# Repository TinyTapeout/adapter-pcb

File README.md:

# Tiny Tapeout adapter PCBs

For interfacing between different versions of the [carrier board](https://github.com/TinyTapeout/breakout-pcb/) and the [demo board](https://github.com/TinyTapeout/tt-demo-pcb)

## TT04 carrier board to TT06 demo board

## TT06 carrier board to TT04 demo board

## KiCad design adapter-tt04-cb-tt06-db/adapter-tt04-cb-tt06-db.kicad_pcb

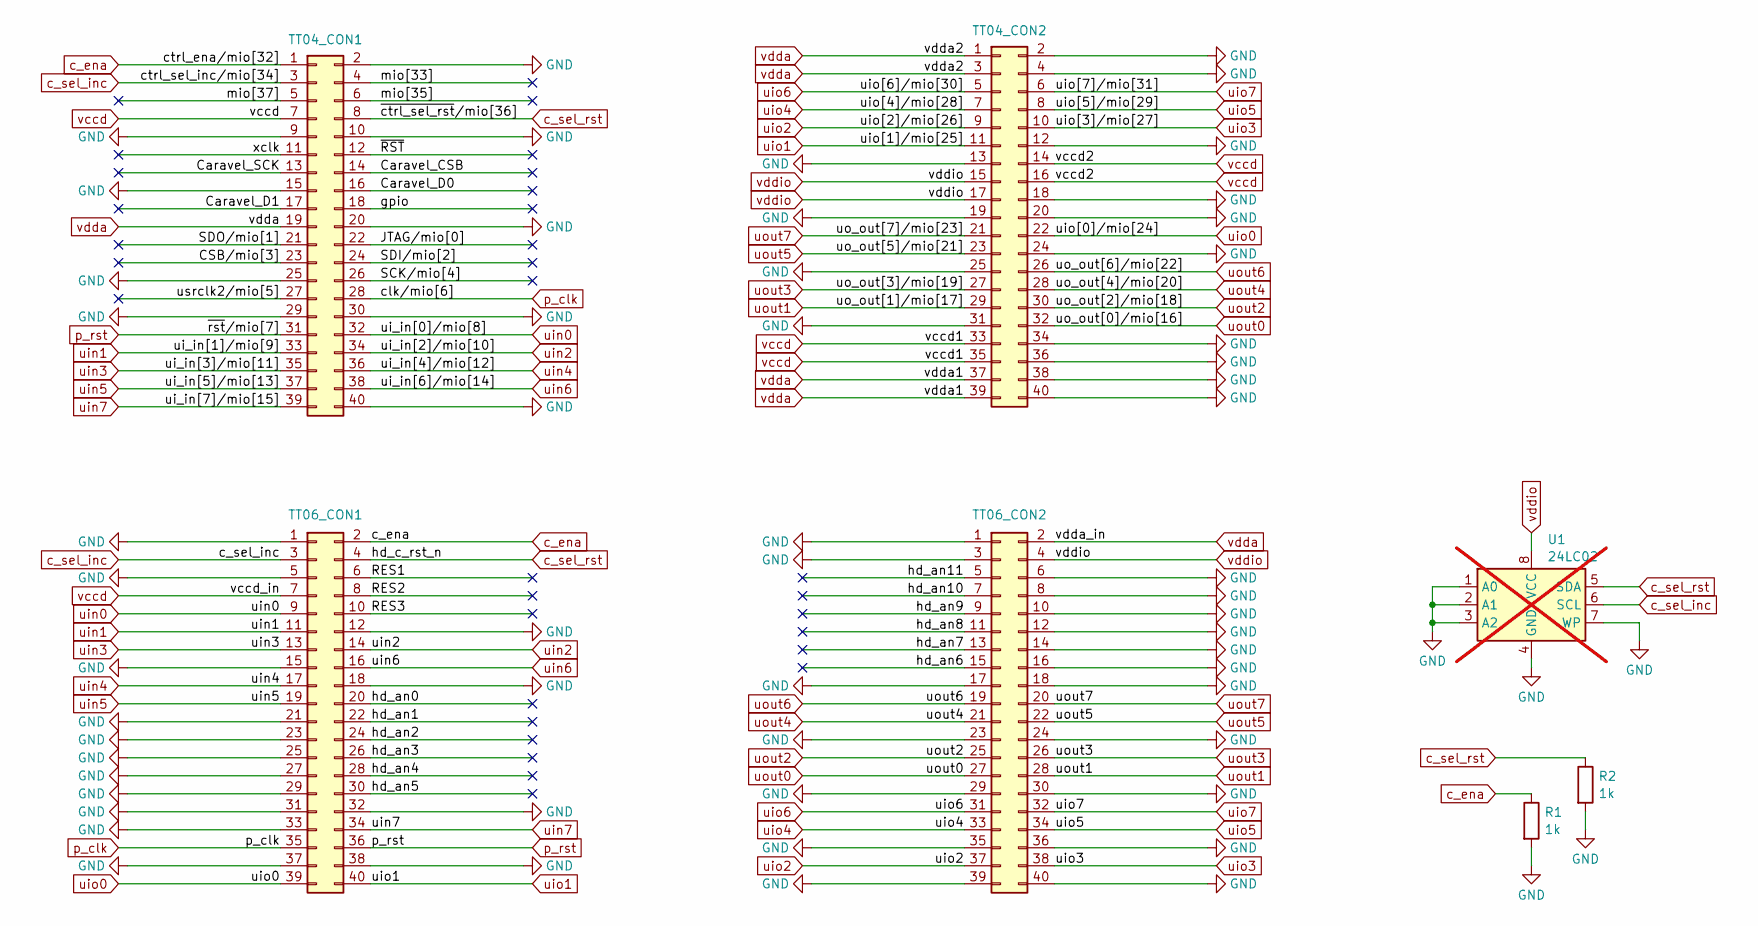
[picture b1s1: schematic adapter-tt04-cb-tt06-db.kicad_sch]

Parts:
R1, R2: 1k; R_0402_1005Metric; JLC C11702
TT04_CON1, TT04_CON2: PinHeader_2x20_P2.54mm_Vertical_SMD; MPN 95157-440LF; DigikeyPN 609-3124-ND
TT06_CON1, TT06_CON2: FH-00148_PinSocket_2x20_P2.54mm; MPN NPTC202KFMS-RC; DigikeyPN S5690-ND
U1: 24LC02; DFN-8-1EP_3x2mm_P0.5mm_EP1.75x1.45mm; MPN 24LC02BT-I/MC; DigikeyPN 24LC02BT-I/MCCT-ND; not fitted

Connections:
/CSB/mio[3]: TT04_CON1.23
/Caravel_CSB: TT04_CON1.14
/Caravel_D0: TT04_CON1.16
/Caravel_D1: TT04_CON1.17
/Caravel_SCK: TT04_CON1.13
/JTAG/mio[0]: TT04_CON1.22
/RES1: TT06_CON1.6
/RES2: TT06_CON1.8
/RES3: TT06_CON1.10
/SCK/mio[4]: TT04_CON1.26
/SDI/mio[2]: TT04_CON1.24
/SDO/mio[1]: TT04_CON1.21
/gpio: TT04_CON1.18
/hd_an0: TT06_CON1.20
/hd_an1: TT06_CON1.22
/hd_an2: TT06_CON1.24
/hd_an3: TT06_CON1.26
/hd_an4: TT06_CON1.28
/hd_an5: TT06_CON1.30
/hd_an6: TT06_CON2.15
/hd_an7: TT06_CON2.13
/hd_an8: TT06_CON2.11
/hd_an9: TT06_CON2.9
/hd_an10: TT06_CON2.7
/hd_an11: TT06_CON2.5
/mio[33]: TT04_CON1.4
/mio[35]: TT04_CON1.6
/mio[37]: TT04_CON1.5
/usrclk2/mio[5]: TT04_CON1.27
/xclk: TT04_CON1.11
/~RST: TT04_CON1.12
GND: R1.2, R2.2, TT04_CON1.2, TT04_CON1.9, TT04_CON1.10, TT04_CON1.15, TT04_CON1.20, TT04_CON1.25, TT04_CON1.29, TT04_CON1.30, TT04_CON1.40, TT04_CON2.2, TT04_CON2.4, TT04_CON2.12, TT04_CON2.13, TT04_CON2.18, TT04_CON2.19, TT04_CON2.20, TT04_CON2.24, TT04_CON2.25, TT04_CON2.31, TT04_CON2.34, TT04_CON2.36, TT04_CON2.38, TT04_CON2.40, TT06_CON1.1, TT06_CON1.5, TT06_CON1.12, TT06_CON1.15, TT06_CON1.18, TT06_CON1.21, TT06_CON1.23, TT06_CON1.25, TT06_CON1.27, TT06_CON1.29, TT06_CON1.31, TT06_CON1.32, TT06_CON1.33, TT06_CON1.37, TT06_CON1.38, TT06_CON2.1, TT06_CON2.3, TT06_CON2.6, TT06_CON2.8, TT06_CON2.10, TT06_CON2.12, TT06_CON2.14, TT06_CON2.16, TT06_CON2.17, TT06_CON2.18, TT06_CON2.23, TT06_CON2.24, TT06_CON2.29, TT06_CON2.30, TT06_CON2.35, TT06_CON2.36, TT06_CON2.39, TT06_CON2.40, U1.1 (A0), U1.2 (A1), U1.3 (A2), U1.4 (GND), U1.7 (WP), U1.9
c_ena: R1.1, TT04_CON1.1, TT06_CON1.2
c_sel_inc: TT04_CON1.3, TT06_CON1.3, U1.6 (SCL)
c_sel_rst: R2.1, TT04_CON1.8, TT06_CON1.4, U1.5 (SDA)
p_clk: TT04_CON1.28, TT06_CON1.35
p_rst: TT04_CON1.31, TT06_CON1.36
uin0: TT04_CON1.32, TT06_CON1.9
uin1: TT04_CON1.33, TT06_CON1.11
uin2: TT04_CON1.34, TT06_CON1.14
uin3: TT04_CON1.35, TT06_CON1.13
uin4: TT04_CON1.36, TT06_CON1.17
uin5: TT04_CON1.37, TT06_CON1.19
uin6: TT04_CON1.38, TT06_CON1.16
uin7: TT04_CON1.39, TT06_CON1.34
uio0: TT04_CON2.22, TT06_CON1.39
uio1: TT04_CON2.11, TT06_CON1.40
uio2: TT04_CON2.9, TT06_CON2.37
uio3: TT04_CON2.10, TT06_CON2.38
uio4: TT04_CON2.7, TT06_CON2.33
uio5: TT04_CON2.8, TT06_CON2.34
uio6: TT04_CON2.5, TT06_CON2.31
uio7: TT04_CON2.6, TT06_CON2.32
uout0: TT04_CON2.32, TT06_CON2.27
uout1: TT04_CON2.29, TT06_CON2.28
uout2: TT04_CON2.30, TT06_CON2.25
uout3: TT04_CON2.27, TT06_CON2.26
uout4: TT04_CON2.28, TT06_CON2.21
uout5: TT04_CON2.23, TT06_CON2.22
uout6: TT04_CON2.26, TT06_CON2.19
uout7: TT04_CON2.21, TT06_CON2.20
vccd: TT04_CON1.7, TT04_CON2.14, TT04_CON2.16, TT04_CON2.33, TT04_CON2.35, TT06_CON1.7
vdda: TT04_CON1.19, TT04_CON2.1, TT04_CON2.3, TT04_CON2.37, TT04_CON2.39, TT06_CON2.2
vddio: TT04_CON2.15, TT04_CON2.17, TT06_CON2.4, U1.8 (VCC)

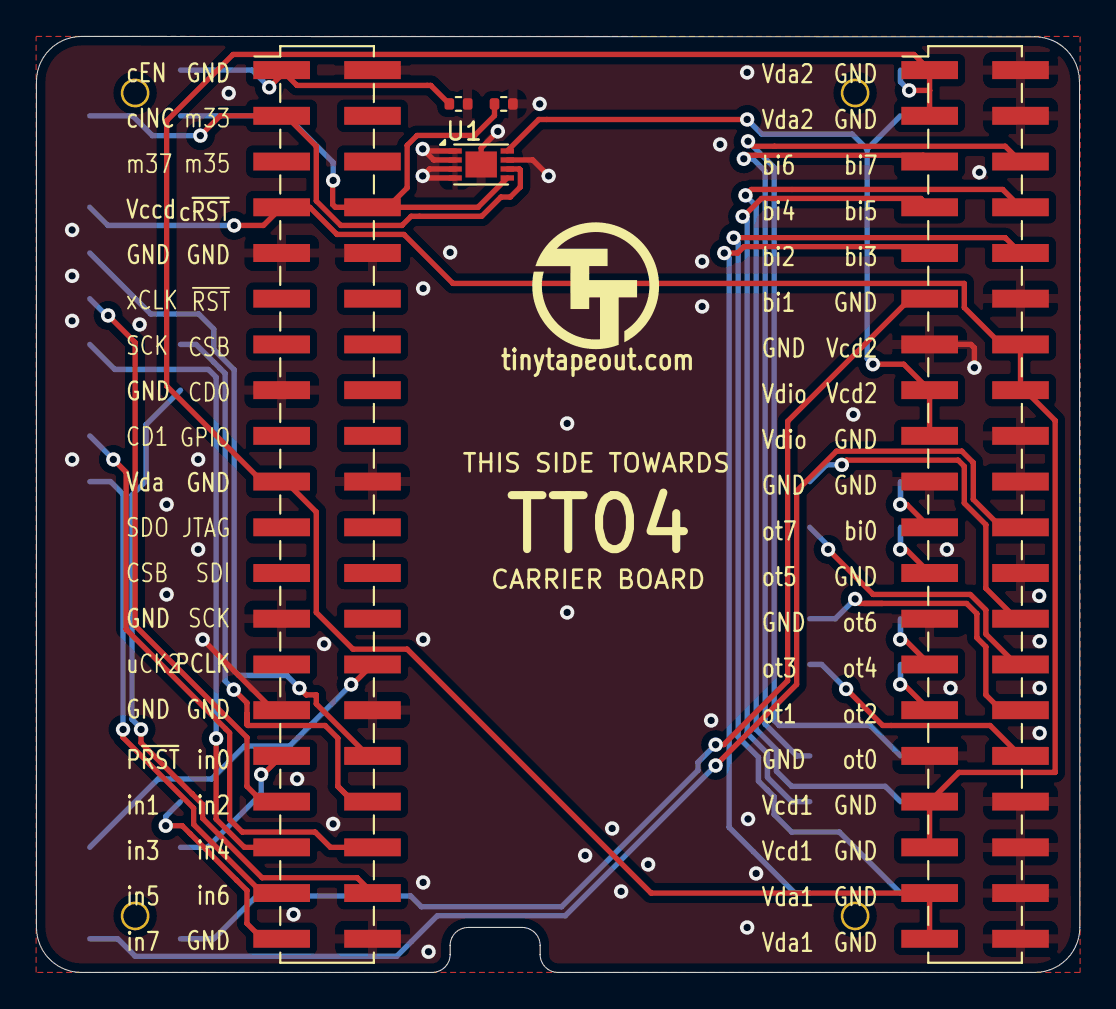
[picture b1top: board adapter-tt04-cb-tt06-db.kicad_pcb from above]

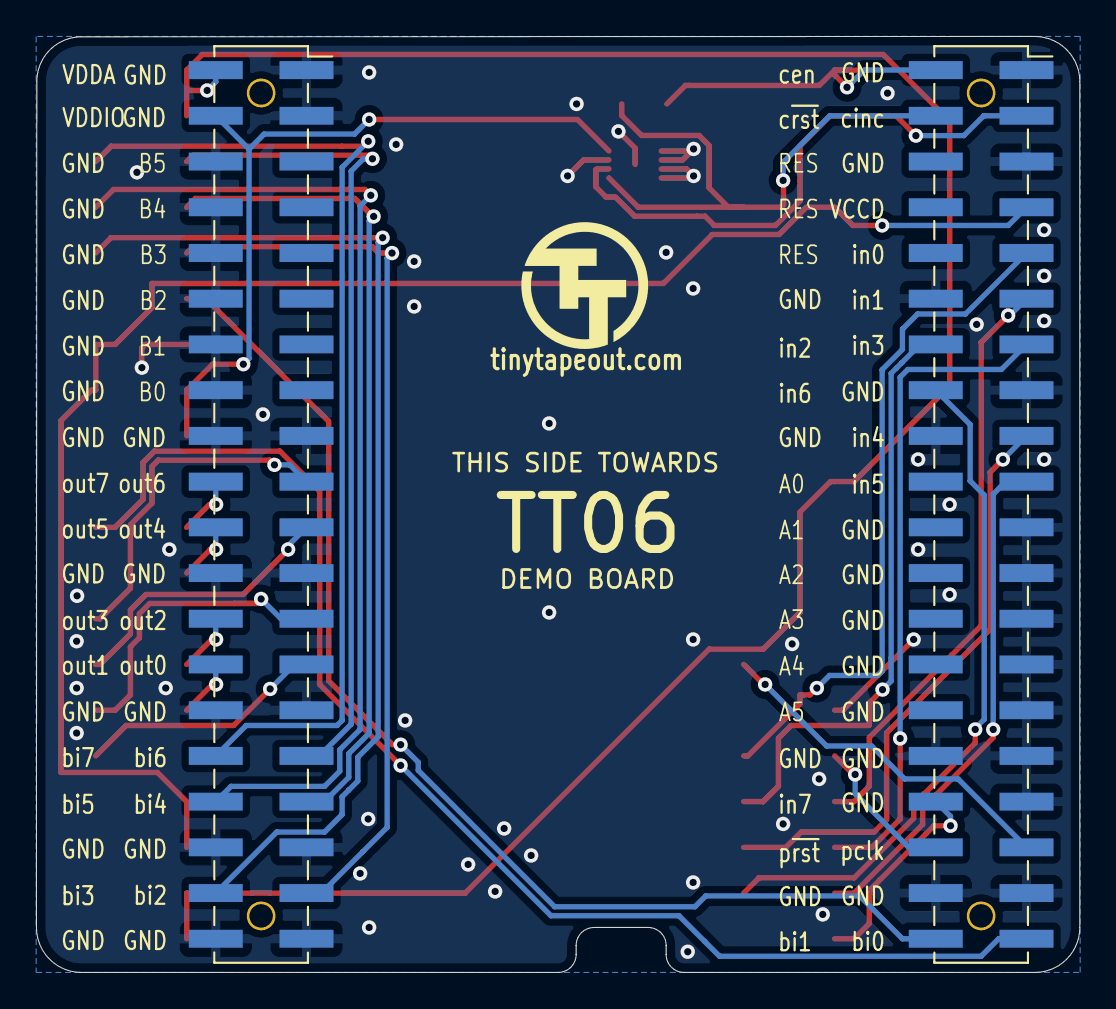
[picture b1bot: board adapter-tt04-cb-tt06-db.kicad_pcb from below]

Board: 2 copper layers, 58.0 x 52.0 mm, 9 parts (3 on the bottom side), 33 nets.

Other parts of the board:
TTLOGO: TT_logo
TTLOGO#2: TT_logo

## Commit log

2024-08-14 feat: add files to version control
